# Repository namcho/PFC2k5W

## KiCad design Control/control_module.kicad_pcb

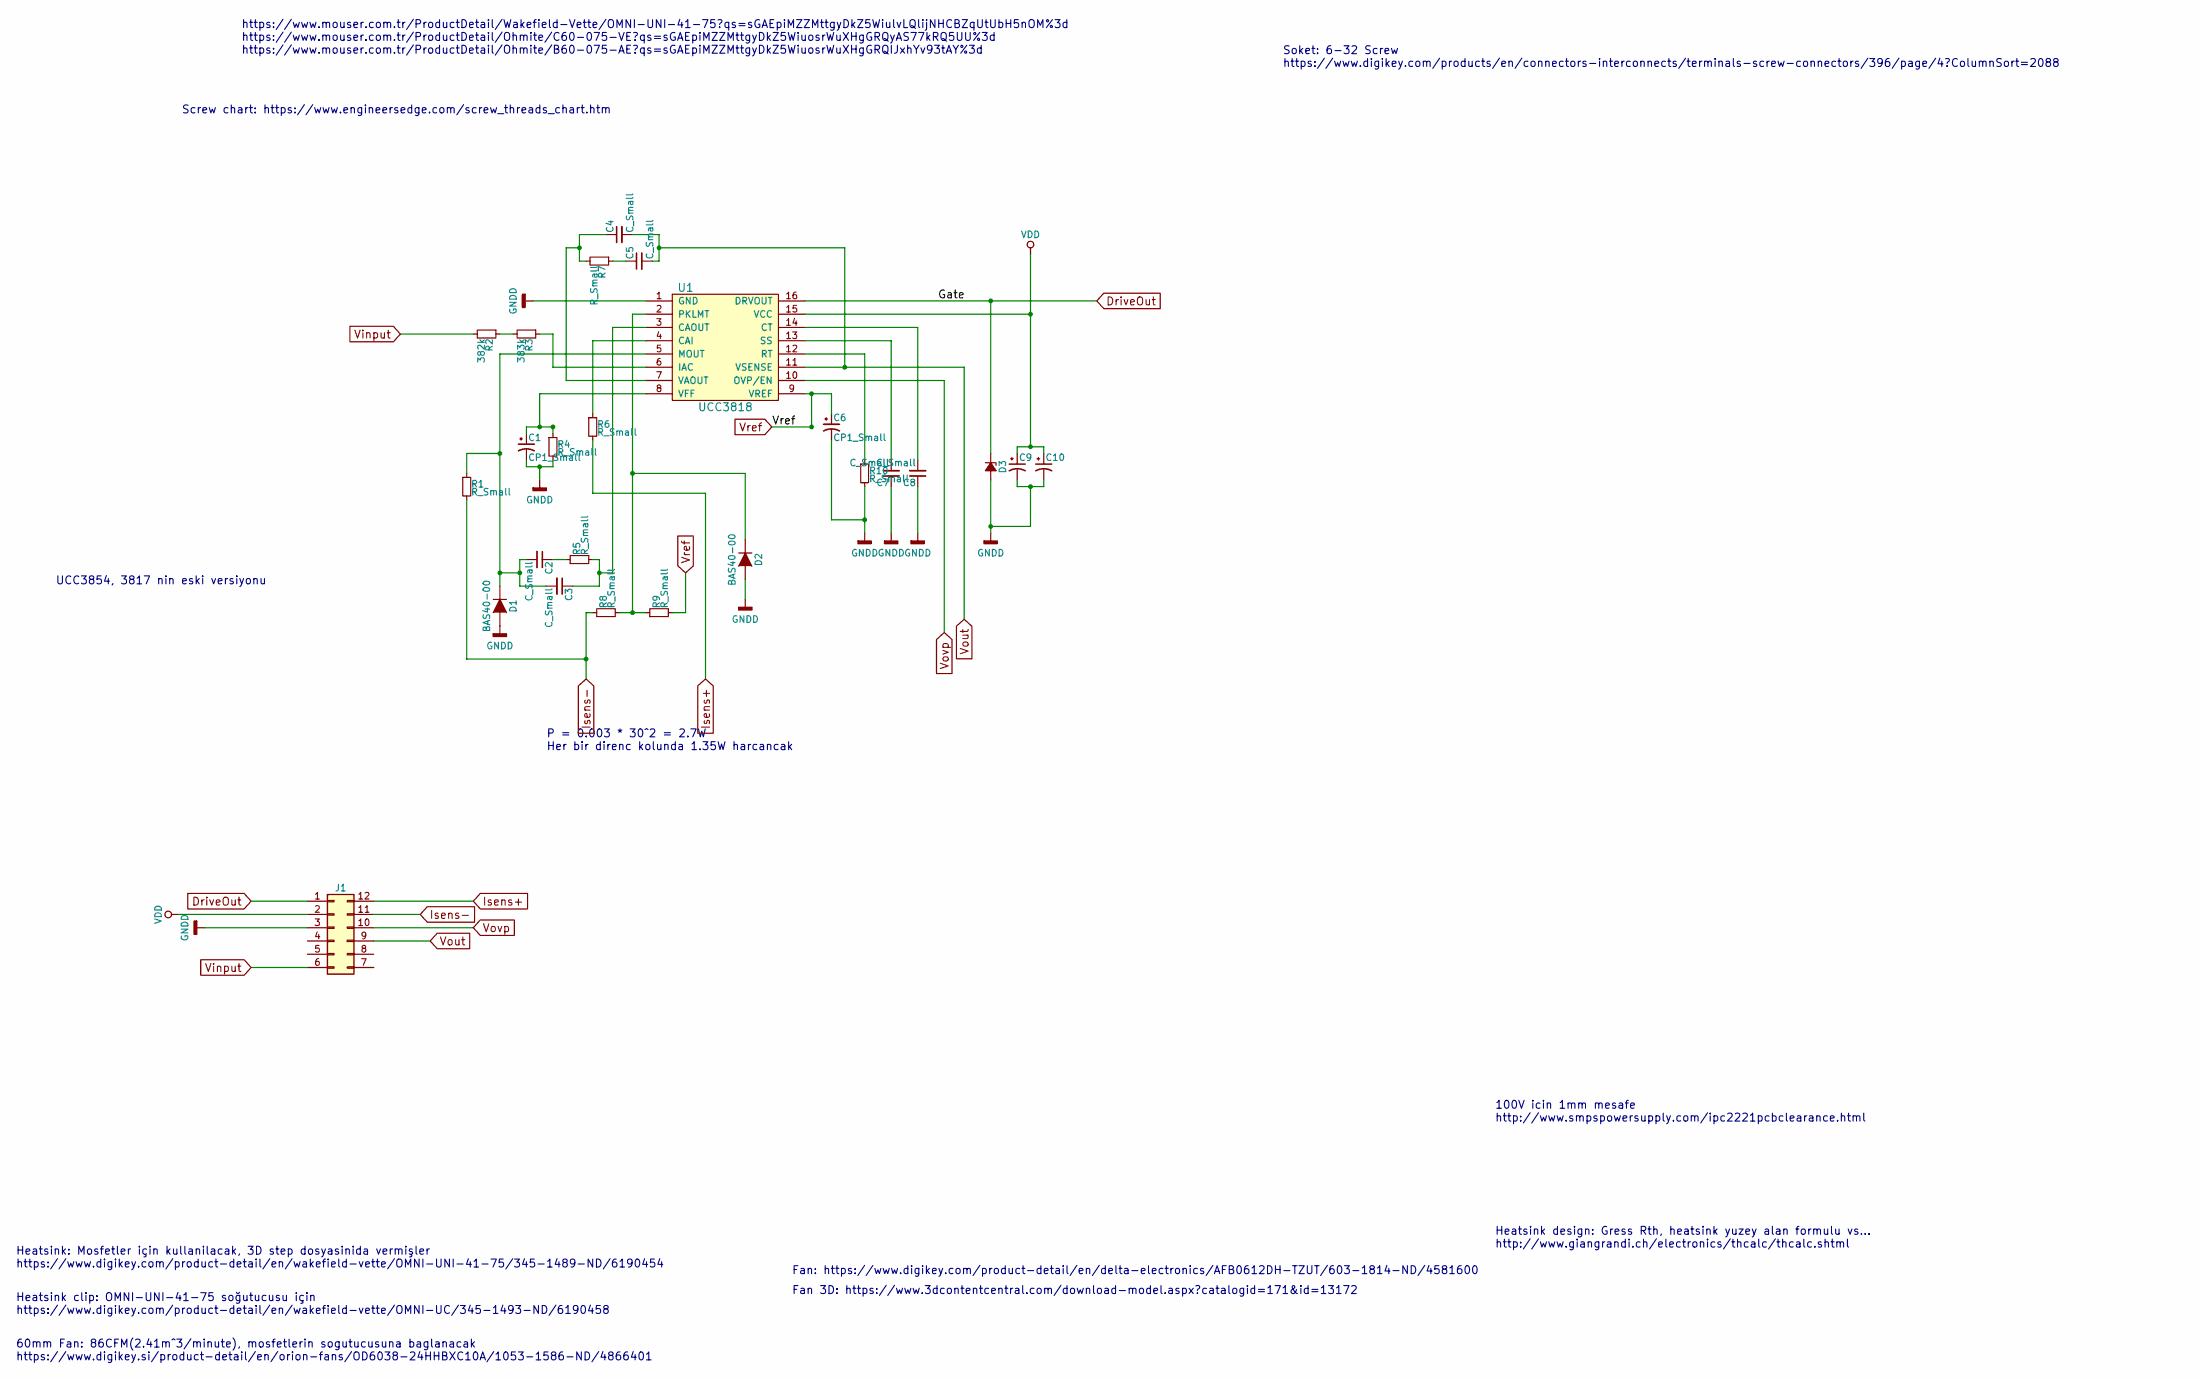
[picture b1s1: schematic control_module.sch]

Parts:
C1, C6: CP1_Small; C_1206_HandSoldering
C2, C3, C4, C5, C7, C8: C_Small; C_0805_HandSoldering
C9: 1u; C_1206_HandSoldering
C10: 100u; CP_Elec_8x10
D1, D2: BAS40-00; SOT-23_Handsoldering
D3: D_Zener_Small_ALT; D_SOD-123
J1: Conn_02x06_Counter_Clockwise; Harwin_M55_7101242R
R1, R4, R5, R6, R7, R8, R9, R10: R_Small; R_0805_HandSoldering
R2: 382k; R_1206_HandSoldering
R3: 383k; R_1206_HandSoldering
U1: UCC3818; SOIC-16W_7.5x10.3mm_Pitch1.27mm

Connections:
DriveOut: D3.1 (K), J1.1, U1.16 (DRVOUT)
GNDD: C1.2, C6.2, C7.1, C8.1, C9.2, C10.2, D1.1 (A), D2.1 (A), D3.2 (A), J1.3, R4.2, R10.2, U1.1 (GND)
Isens+: J1.12, R6.2
Isens-: J1.11, R1.2, R8.1
unnamed: C1.1, R4.1, U1.8 (VFF)
unnamed: C2.1, R5.1
unnamed: C2.2, C3.2, D1.3 (K), R1.1, U1.5 (MOUT)
unnamed: C3.1, R5.2, U1.3 (CAOUT)
unnamed: C4.1, R7.2, U1.7 (VAOUT)
unnamed: C5.1, R7.1
unnamed: C7.2, U1.13 (SS)
unnamed: C8.2, U1.14 (CT)
unnamed: D2.3 (K), R8.2, R9.1, U1.2 (PKLMT)
unnamed: R2.1, R3.2
unnamed: R3.1, U1.6 (IAC)
unnamed: R6.1, U1.4 (CAI)
unnamed: R10.1, U1.12 (RT)
VDD: C9.1, C10.1, J1.2, U1.15 (VCC)
Vinput: J1.6, R2.2
Vout: C4.2, C5.2, J1.9, U1.11 (VSENSE)
Vovp: J1.10, U1.10 (OVP/EN)
Vref: C6.1, R9.2, U1.9 (VREF)

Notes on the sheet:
Heatsink design: Gress Rth, heatsink yuzey alan formulu vs... http://www.giangrandi.ch/electronics/thcalc/thcalc.shtml
https://www.mouser.com.tr/ProductDetail/Wakefield-Vette/OMNI-UNI-41-75?qs=sGAEpiMZZMttgyDkZ5WiulvLQlijNHCBZqUtUbH5nOM%3d https://www.mouser.com.tr/ProductDetail/Ohmite/C60-075-VE?qs=sGAEpiMZZMttgyDkZ5WiuosrWuXHgGRQyAS77kRQ5UU%3d https://www.mouser.com.tr/ProductDetail/Ohmite/B60-075-AE?qs=sGAEpiMZZ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
60mm Fan: 86CFM(2.41m^3/minute), mosfetlerin sogutucusuna baglanacak https://www.digikey.si/product-detail/en/orion-fans/OD6038-24HHBXC10A/1053-1586-ND/4866401
Heatsink clip: OMNI-UNI-41-75 soğutucusu için https://www.digikey.com/product-detail/en/wakefield-vette/OMNI-UC/345-1493-ND/6190458
Heatsink: Mosfetler için kullanilacak, 3D step dosyasinida vermişler https://www.digikey.com/product-detail/en/wakefield-vette/OMNI-UNI-41-75/345-1489-ND/6190454
Screw chart: https://www.engineersedge.com/screw_threads_chart.htm
Fan: https://www.digikey.com/product-detail/en/delta-electronics/AFB0612DH-TZUT/603-1814-ND/4581600
Fan 3D: https://www.3dcontentcentral.com/download-model.aspx?catalogid=171&id=13172
Soket: 6-32 Screw https://www.digikey.com/products/en/connectors-interconnects/terminals-screw-connectors/396/page/4?ColumnSort=2088
100V icin 1mm mesafe http://www.smpspowersupply.com/ipc2221pcbclearance.html
P = 0.003 * 30^2 = 2.7W Her bir direnc kolunda 1.35W harcancak
UCC3854, 3817 nin eski versiyonu

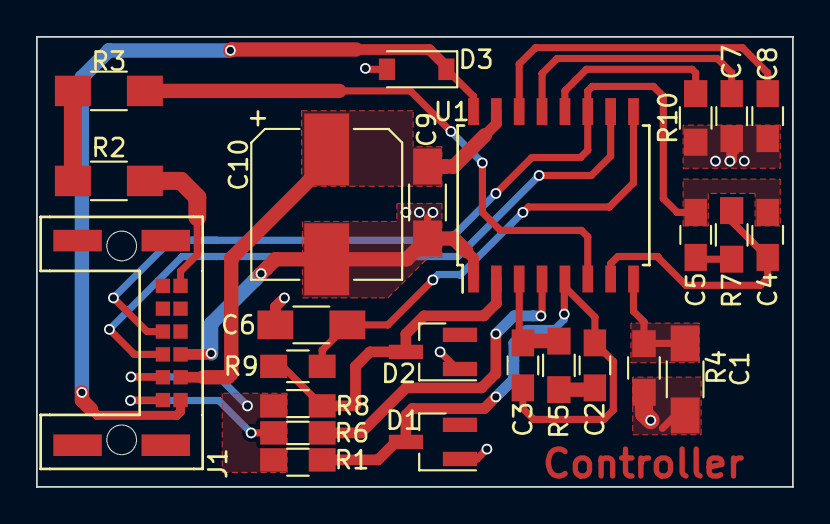
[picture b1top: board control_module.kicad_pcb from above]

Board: 2 copper layers, 42.0 x 25.0 mm, 25 parts (0 on the bottom side), 22 nets.

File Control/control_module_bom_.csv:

Component,Description,Part,References,Value,Footprint,Quantity Per PCB,Datasheet
1,Polarised capacitor,CP1_Small,C10,100u,CP_Elec_8x10,1,
2,Polarised capacitor,CP1_Small,C9,1u,C_1206_HandSoldering,1,
3,Polarised capacitor,CP1_Small,C1 C6,CP1_Small,C_1206_HandSoldering,2,
4,Unpolarized capacitor,C_Small,C2 C3 C4 C5 C7 C8,C_Small,C_0805_HandSoldering,6,
5,Diode,BAS40-00,D1 D2,BAS40-00,SOT-23_Handsoldering,2,http://www.vishay.com/docs/85701/bas40v.pdf
6,"Zener Diode, small symbol, alternativ symbol",D_Zener_Small_ALT,D3,D_Zener_Small_ALT,D_SOD-123,1,http://www.semicon.sanken-ele.co.jp/sk_content/sjpz-n18_ds_en.pdf
7,"Generic connector, double row, 02x06, counter clockwise pin numbering scheme (similar to DIP packge numbering)",Conn_02x06_Counter_Clockwise,J1,Conn_02x06_Counter_Clockwise,Harwin_M55_7101242R,1,https://cdn.harwin.com/pdfs/M55-710.pdf
8,"Resistor, small symbol",R_Small,R2,382k,R_1206_HandSoldering,1,
9,"Resistor, small symbol",R_Small,R3,383k,R_1206_HandSoldering,1,
10,"Resistor, small symbol",R_Small,R1 R4 R5 R6 R7 R8 R9 R10,R_Small,R_0805_HandSoldering,8,
11,,UCC3818,U1,UCC3818,SOIC-16W_7.5x10.3mm_Pitch1.27mm,1,





Component Groups:,11
Component Count:,25
Fitted Components:,25
Number of PCBs:,1
Total components:,25
Schematic Version:,
Schematic Date:,
BoM Date:,10.06.2018 21:46:59
Schematic Source:,D:/KiCAD/Projects/PFC2k5W/Control/control_module.sch
KiCad Version:,Eeschema 4.0.7

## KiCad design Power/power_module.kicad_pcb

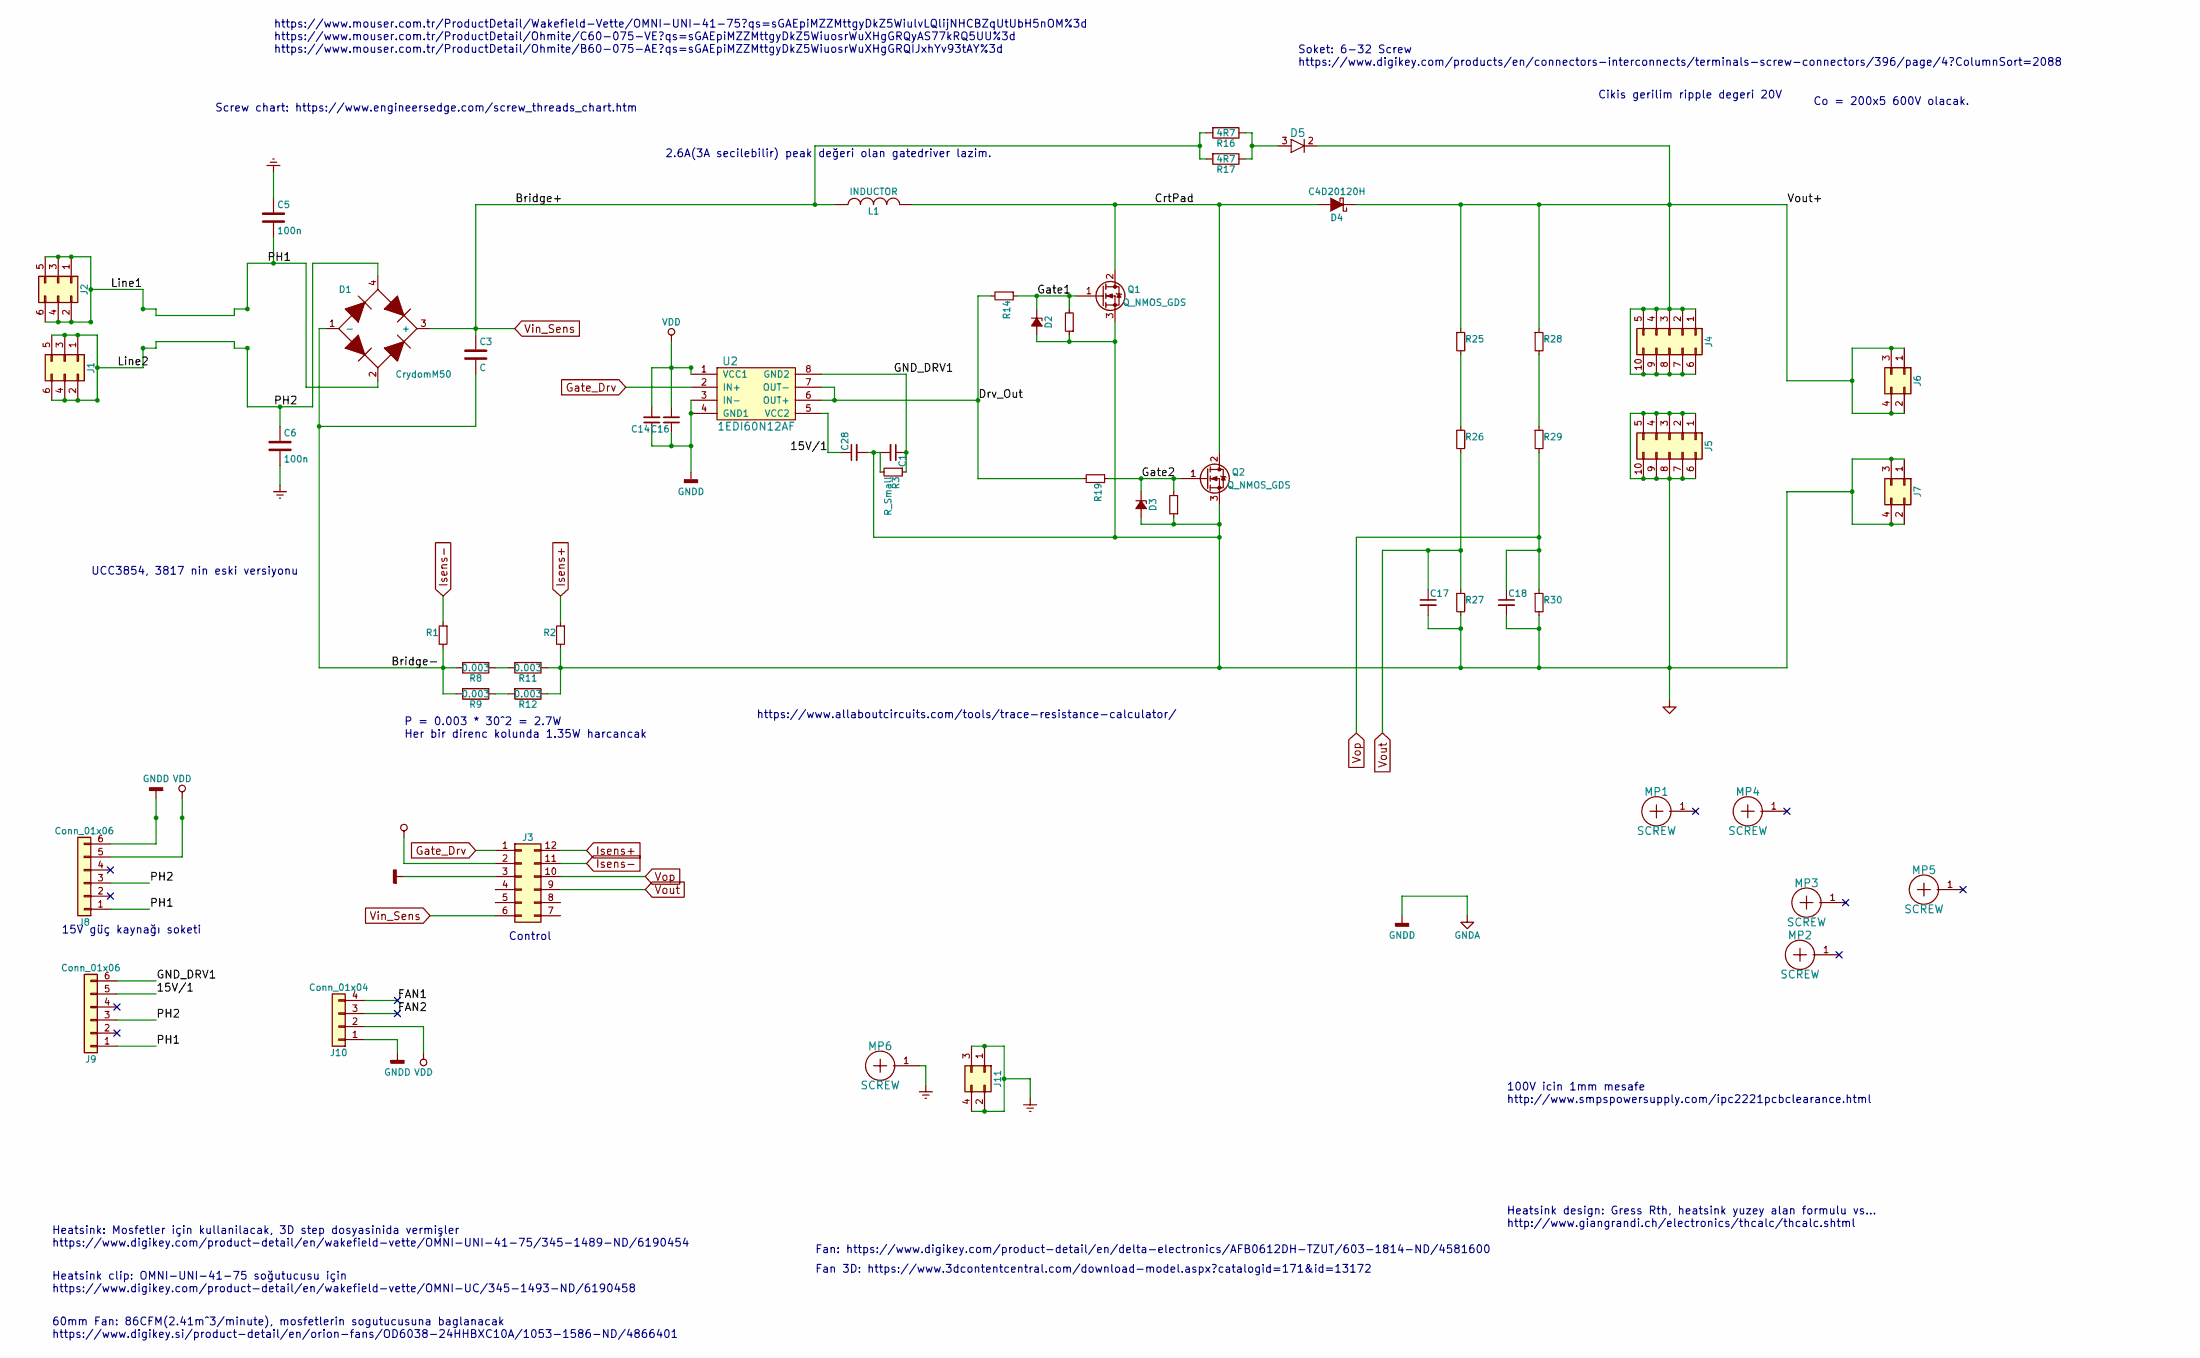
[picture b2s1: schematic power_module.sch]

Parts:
C1, C16, C28: 1u; C_1206_HandSoldering
C3: C; C_Rect_L18.0mm_W5.0mm_P15.00mm_FKS3_FKP3
C5, C6: 100n; C_Rect_L18.0mm_W8.0mm_P15.00mm_FKS3_FKP3
C14: 10n; C_0805_HandSoldering
C17, C18: C_Small; C_0805_HandSoldering
D1: CrydomM50; CrydomM50x_Fixed
D2, D3: D_Zener_Small_ALT; D_SOD-123
D4: C4D20120H; TO-247-2_Vertical
D5: IDW75E60; TO-247_TO-3P_Vertical
J1, J2: Conn_02x03_Odd_Even; Conn_6pins_30A
J3: Conn_02x06_Counter_Clockwise; Harwin_M55_6001242R
J4, J5: Conn_02x05_Top_Bottom; Hirose_FX30B_5P_DSA
J6, J7, J11: Conn_02x02_Odd_Even; Conn_4pins_15A
J8, J9: Conn_01x06; Pin_Header_Straight_1x06_Pitch2.54mm
J10: Conn_01x04; Pin_Header_Straight_1x04_Pitch2.54mm
L1: INDUCTOR; OD_77.80xID_39.34xHT_25.85_Vertical
MP1, MP2, MP3, MP4, MP5, MP6: SCREW; SCREW_3mm
Q1, Q2: Q_NMOS_GDS; TO-247_TO-3P_Vertical
R1, R2, R14, R19, R25, R26, R27, R28, R29, R30: R_Small; R_1206_HandSoldering
R3: R_Small; R_0805_HandSoldering
R8, R9, R11, R12: 0.003; R_2512_HandSoldering
R16, R17: 4R7; R_2512_HandSoldering
R31, R32: 10k; R_1206_HandSoldering
U2: 1EDI60N12AF; SOIC-8_3.9x4.9mm_Pitch1.27mm

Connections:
/15V/1: C28.1, J9.5, U2.5 (VCC2)
/Bridge-: C3.2, D1.1 (-), R1.2, R8.2, R9.2
/CrtPad: D4.2 (A), L1.1, Q1.2 (D), Q2.2 (D)
/Drv_Out: R14.2, R19.2, U2.6 (OUT+), U2.7 (OUT-)
/FAN1: J10.4
/FAN2: J10.3
/GND_DRV1: C1.1, J9.6, R3.1, U2.8 (GND2)
/Gate1: D2.1 (K), Q1.1 (G), R14.1, R31.2
/Gate2: D3.1 (K), Q2.1 (G), R19.1, R32.2
/Line1: C5.2, D1.2, J2.1, J2.2, J2.3, J2.4, J2.5, J2.6, J8.1, J9.1
/Line2: C6.1, D1.4, J1.1, J1.2, J1.3, J1.4, J1.5, J1.6, J8.3, J9.3
/Vout+: D4.1 (K), D5.2, J4.1, J4.2, J4.3, J4.4, J4.5, J4.6, J4.7, J4.8, J4.9, J4.10, J6.1, J6.2, J6.3, J6.4, R25.1, R28.1
Earth: C5.1, C6.2, J11.1, J11.2, J11.3, J11.4, MP6.1
GNDA: C1.2, C14.1, C16.1, C17.2, C18.2, C28.2, D2.2 (A), D3.2 (A), J3.3, J5.1, J5.2, J5.3, J5.4, J5.5, J5.6, J5.7, J5.8, J5.9, J5.10, J7.1, J7.2, J7.3, J7.4, J8.6, J10.1, Q1.3 (S), Q2.3 (S), R2.2, R3.2, R11.1, R12.1, R27.2, R30.2, R31.1, R32.1, U2.3 (IN-), U2.4 (GND1)
Gate_Drv: J3.1, U2.2 (IN+)
Isens+: J3.12, R2.1
Isens-: J3.11, R1.1
unnamed: D5.3, R16.1, R17.1
unnamed: R8.1, R11.2
unnamed: R9.1, R12.2
unnamed: R25.2, R26.1
unnamed: R28.2, R29.1
VDD: C14.2, C16.2, J3.2, J8.5, J10.2, U2.1 (VCC1)
Vin_Sens: C3.1, D1.3 (+), J3.6, L1.2, R16.2, R17.2
Vop: C18.1, J3.10, R29.2, R30.1
Vout: C17.1, J3.9, R26.2, R27.1

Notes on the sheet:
15V güç kaynağı soketi
Heatsink design: Gress Rth, heatsink yuzey alan formulu vs... http://www.giangrandi.ch/electronics/thcalc/thcalc.shtml
https://www.mouser.com.tr/ProductDetail/Wakefield-Vette/OMNI-UNI-41-75?qs=sGAEpiMZZMttgyDkZ5WiulvLQlijNHCBZqUtUbH5nOM%3d https://www.mouser.com.tr/ProductDetail/Ohmite/C60-075-VE?qs=sGAEpiMZZMttgyDkZ5WiuosrWuXHgGRQyAS77kRQ5UU%3d https://www.mouser.com.tr/ProductDetail/Ohmite/B60-075-AE?qs=sGAEpiMZZ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
60mm Fan: 86CFM(2.41m^3/minute), mosfetlerin sogutucusuna baglanacak https://www.digikey.si/product-detail/en/orion-fans/OD6038-24HHBXC10A/1053-1586-ND/4866401
Heatsink clip: OMNI-UNI-41-75 soğutucusu için https://www.digikey.com/product-detail/en/wakefield-vette/OMNI-UC/345-1493-ND/6190458
Heatsink: Mosfetler için kullanilacak, 3D step dosyasinida vermişler https://www.digikey.com/product-detail/en/wakefield-vette/OMNI-UNI-41-75/345-1489-ND/6190454
2.6A(3A secilebilir) peak değeri olan gatedriver lazim.
Screw chart: https://www.engineersedge.com/screw_threads_chart.htm
Fan: https://www.digikey.com/product-detail/en/delta-electronics/AFB0612DH-TZUT/603-1814-ND/4581600
Fan 3D: https://www.3dcontentcentral.com/download-model.aspx?catalogid=171&id=13172
Soket: 6-32 Screw https://www.digikey.com/products/en/connectors-interconnects/terminals-screw-connectors/396/page/4?ColumnSort=2088
100V icin 1mm mesafe http://www.smpspowersupply.com/ipc2221pcbclearance.html
P = 0.003 * 30^2 = 2.7W Her bir direnc kolunda 1.35W harcancak
Cikis gerilim ripple degeri 20V
UCC3854, 3817 nin eski versiyonu
Co = 200x5 600V olacak.
Control
https://www.allaboutcircuits.com/tools/trace-resistance-calculator/

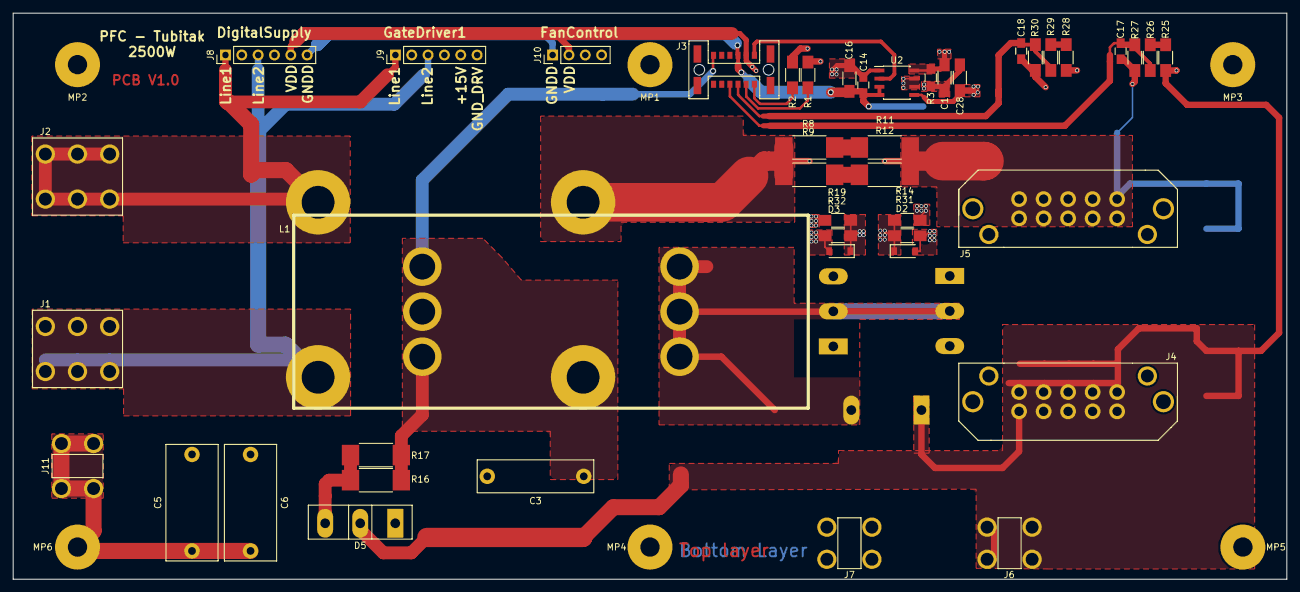
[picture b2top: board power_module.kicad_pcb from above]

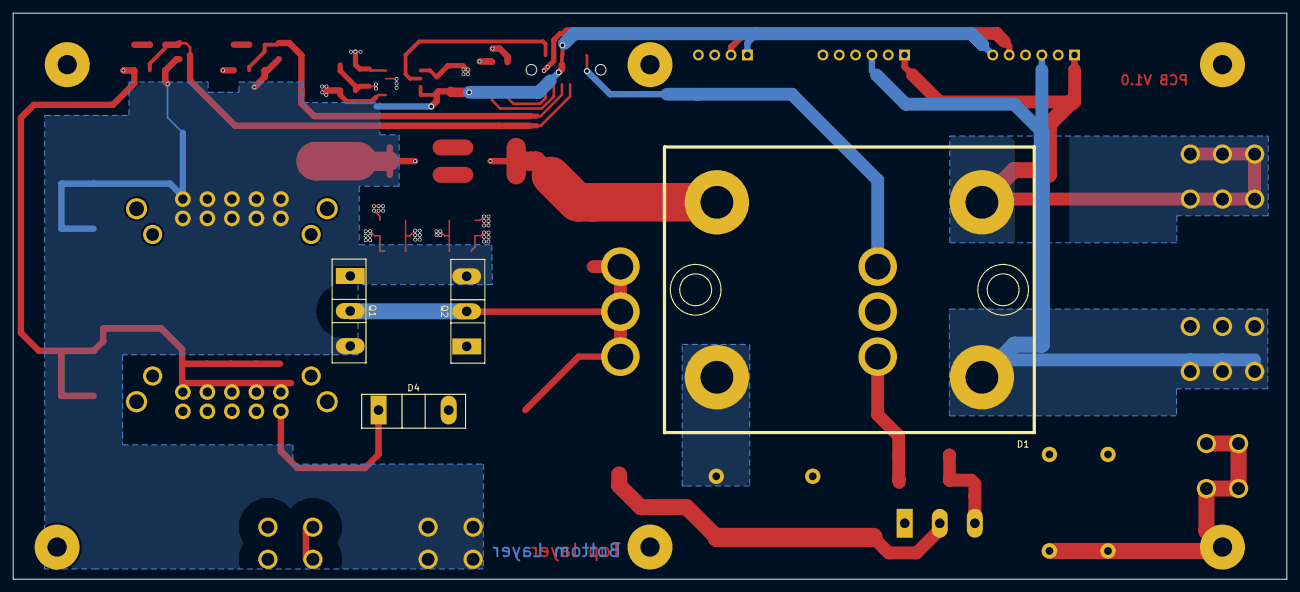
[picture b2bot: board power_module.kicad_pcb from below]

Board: 4 copper layers, 198.0 x 88.0 mm, 54 parts (4 on the bottom side), 24 nets.

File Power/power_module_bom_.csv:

Component,Description,Part,References,Value,Footprint,Quantity Per PCB,Datasheet
1,Unpolarized capacitor,C,C5 C6,100n,C_Rect_L18.0mm_W8.0mm_P15.00mm_FKS3_FKP3,2,
2,Unpolarized capacitor,C_Small,C14,10n,C_0805_HandSoldering,1,
3,Unpolarized capacitor,C_Small,C1 C16 C28,1u,C_1206_HandSoldering,3,
4,Unpolarized capacitor,C,C2 C4,C,CP_Axial_L30.0mm_D10.0mm_P35.00mm_Horizontal,2,
5,Unpolarized capacitor,C,C3,C,C_Rect_L18.0mm_W5.0mm_P15.00mm_FKS3_FKP3,1,
6,Unpolarized capacitor,C_Small,C17 C18,C_Small,C_0805_HandSoldering,2,
7,Diode schottky,C5D50065D,D7,C5D50065D,TO-247_TO-3P_Vertical,1,
8,Diode bridge,CrydomM50,D1,CrydomM50,CrydomM50x_Fixed,1,http://www.crydom.com/en/products/catalog/m50-diode-series-p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
9,"Zener Diode, small symbol, alternativ symbol",D_Zener_Small_ALT,D2 D3,D_Zener_Small_ALT,D_SOD-123,2,https://en.wikipedia.org/wiki/Zener_diode
10,,IDW75E60,D5,IDW75E60,TO-247_TO-3P_Vertical,1,https://www.infineon.com/dgdl/IDW75E60_V2_1.pdf?folderId=db3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
11,EMI 2-inductor-filter,EMI_Filter_CommonMode,FL1,EMI_Filter_CommonMode,RB6522_Size4,1,http://www.murata.com/~/media/webrenewal/support/library/cat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
12,"Generic connector, single row, 01x04",Conn_01x04,J10,Conn_01x04,Pin_Header_Straight_1x04_Pitch2.54mm,1,
13,"Generic connector, single row, 01x06",Conn_01x06,J8 J9,Conn_01x06,Pin_Header_Straight_1x06_Pitch2.54mm,2,
14,"Generic connector, double row, 02x02, odd/even pin numbering scheme (row 1 odd numbers, row 2 even numbers)",Conn_02x02_Odd_Even,J6 J7 J11,Conn_02x02_Odd_Even,Conn_4pins_15A,3,
15,"Generic connector, double row, 02x03, odd/even pin numbering scheme (row 1 odd numbers, row 2 even numbers)",Conn_02x03_Odd_Even,J1 J2,Conn_02x03_Odd_Even,Conn_6pins_30A,2,
16,"Generic connector, double row, 02x05, top/bottom pin numbering scheme (row 1: 1...pins_per_row, row2: pins_per_row+1 ... num_pins)",Conn_02x05_Top_Bottom,J4 J5,Conn_02x05_Top_Bottom,Hirose_FX30B_5P_DSA,2,http://www.mouser.com/catalog/specsheets/Hirose_FX30B%20Series.pdf
17,"Generic connector, double row, 02x06, counter clockwise pin numbering scheme (similar to DIP packge numbering)",Conn_02x06_Counter_Clockwise,J3,Conn_02x06_Counter_Clockwise,Harwin_M55_6001242R,1,https://www.mouser.com.tr/datasheet/2/181/M55-60X-1286666.pdf
18,,INDUCTOR,L1,INDUCTOR,OD_77.80xID_39.34xHT_25.85_Vertical,1,
19,,SCREW,MP1 MP2 MP3 MP4 MP5 MP6,SCREW,SCREW_3mm,6,
20,Transistor N-MOSFET with substrate diode (general),Q_NMOS_GDS,Q1 Q2,Q_NMOS_GDS,TO-247_TO-3P_Vertical,2,
21,Resistor,R,R8 R9 R11 R12,0.003,R_2512_HandSoldering,4,
22,"Resistor, small symbol",R_Small,R31 R32,10k,R_1206_HandSoldering,2,
23,Resistor,R,R16 R17,4R7,R_2512_HandSoldering,2,
24,"Resistor, small symbol",R_Small,R1 R2 R14 R19 R25 R26 R27 R28 R29 R30,R_Small,R_1206_HandSoldering,10,
25,"Resistor, small symbol",R_Small,R3,R_Small,R_0805_HandSoldering,1,
26,,1EDI60N12AF,U2,1EDI60N12AF,SOIC-8_3.9x4.9mm_Pitch1.27mm,1,





Component Groups:,26
Component Count:,57
Fitted Components:,57
Number of PCBs:,1
Total components:,57
Schematic Version:,
Schematic Date:,
BoM Date:,10.06.2018 20:18:45
Schematic Source:,D:\KiCAD\Projects\PFC2k5W\Power\power_module.sch
KiCad Version:,Eeschema 4.0.7

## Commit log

2018-05-13 Guc kati semasi cizildi. Giristen cikisa dogru bir hat olacak sekilde layout yapildi.
2018-05-13 Mevcut yerlesime gore kaba cizim yapildi.
2018-05-15 Guc akisindaki hat/poligonlar tamamlandi.
2018-05-16 Poligon eklemeleri yapildi. Hatlar iyilestirildi.
2018-05-17 Kontrol karti semasi cizildi. Layout yerlestirme yapildi.
2018-05-18 Kontrolcu karti icin layout islemi tamamlandi.
2018-06-10 Güc kartina EMI filtresi eklendi. Güc kartindaki mosfet driver + ve - ile beslenebilecek sekilde duzenlendi. Güc ve kontrol kartlari icin BOM uretildi.
2018-06-25 Hatali Mosfet paketi duzeltildi. EMI filtre kaldirildi ve kart boyu kisaldi. TO247-2 paketli boost diyodu kullanildi.
2018-06-25 Mosfet konumlari degistirildi. Layout iyilestirme yapildi.
2018-06-25 Layout iyilestirmesi. Cikis soketleri kartin sag alt kosesine alindi.
2018-06-28 Yuksek akim tasiyan hatlara Mask atildi dolayisiyla bu hatlara lehim takviyesi yapilabilir.
2018-06-28 Silk katmani duzenlendi. Gerber dosyalari uretildi.
2018-06-28 Kontrol karti gerber dosyalari olusturuldu. Silk katmani duzenlendi.
2018-06-28 Kontrol kartindaki duzenlemeler kayit edildi(Silk-layer).
